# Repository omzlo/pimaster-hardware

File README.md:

# PiMaster HAT Hardware

This repository contains the design files and schematics of the Omzlo PiMaster HAT (Hardware Attached on Top).

See: http://omzlo.com/pimaster

This work is licensed under the [Creative Commons Attribution-ShareAlike 4.0 International Public License][1].

[1]: https://creativecommons.org/licenses/by-sa/4.0/

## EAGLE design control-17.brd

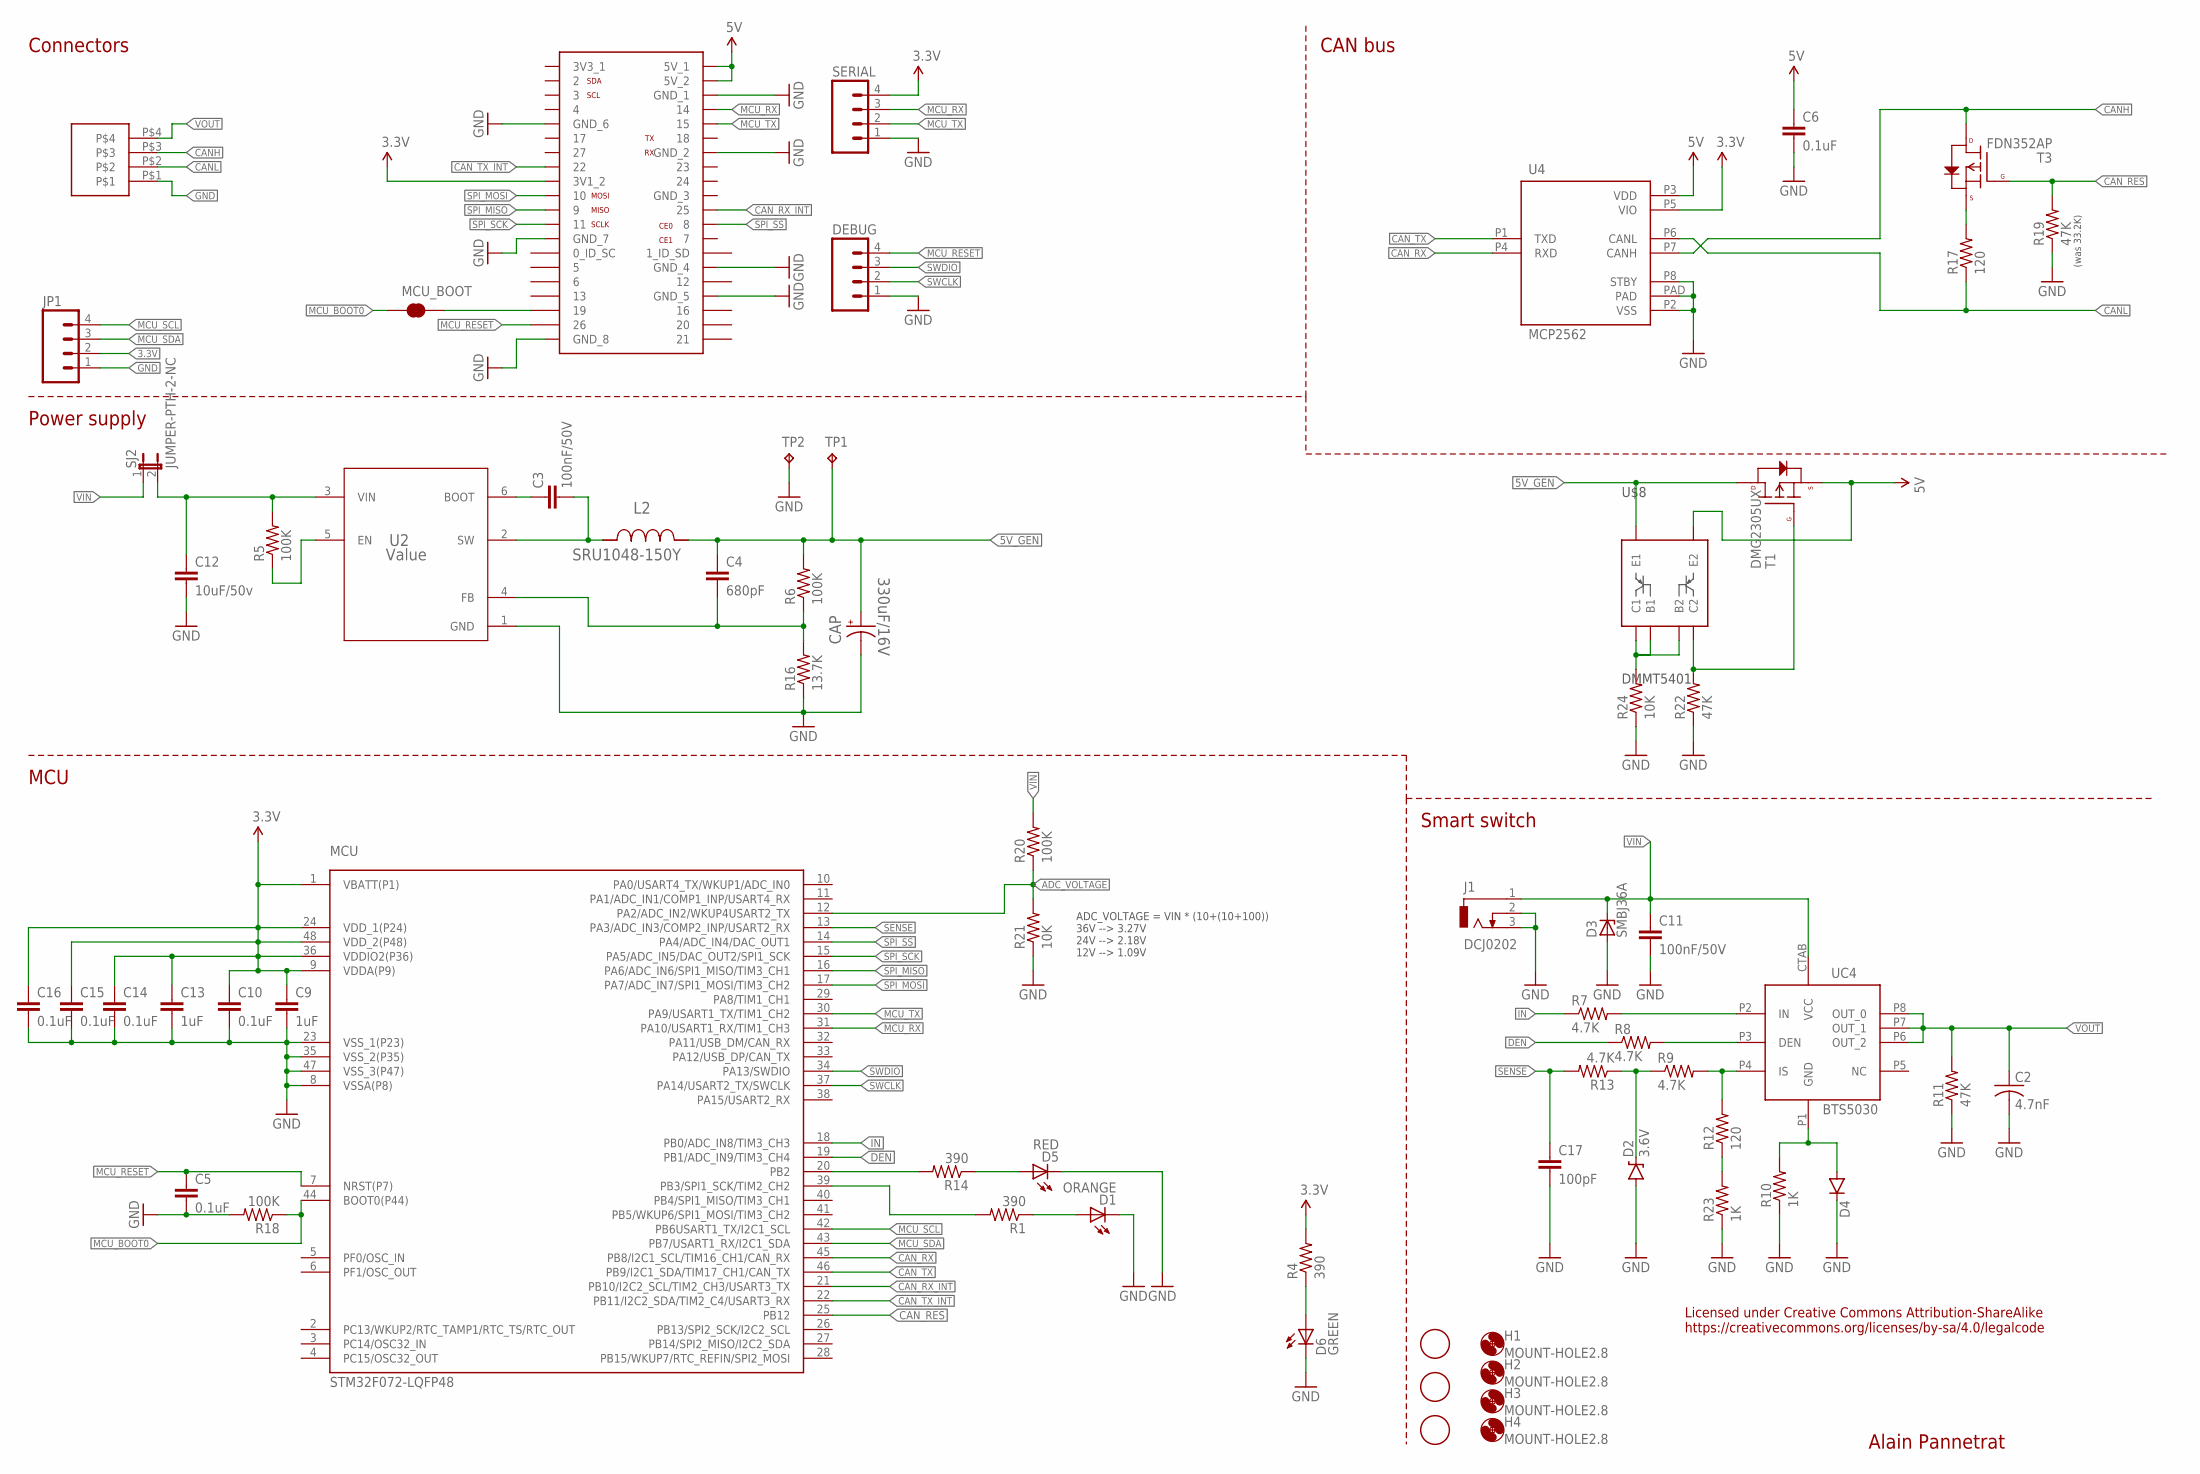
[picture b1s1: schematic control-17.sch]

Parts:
C2: 4.7nF; C0805
C3, C11: 100nF/50V; 0805
C4: 680pF; 0603-CAP
C5, C6, C10, C14, C15, C16: 0.1uF; 0603-CAP
C9, C13: 1uF; 0805
C12: 10uF/50v; 1206
C17: 100pF; 0805
CAP: 330uF/16V; PANASONIC_E
D1: ORANGE; CHIPLED_0805
D2: 3.6V; SOD-323
D3: SMBJ36A; SMB
D4: DIODESMA; SMA-DIODE
D5: RED; CHIPLED_0805
D6: GREEN; CHIPLED_0805
DEBUG: M04PTH; 1X04
H1, H2, H3, H4: MOUNT-HOLE2.8; 2,8
J1: DCJ0202
JP1: M04JST; 1X04-1.5MM_JST
L2: SRU1048-150Y; SRU1048
MCU: STM32F072-LQFP48; LQFP48
MCU_BOOT: JUMPER-PAD-2-NC_BY_TRACE; PAD-JUMPER-2-NC_BY_TRACE_YES_SILK
PI: RASPBERRY-PI-GPIO-SEPARATE; 2X20
R1, R4, R14: 390; R0603
R5, R6, R18, R20: 100K; R0603
R7, R8, R9, R13: 4.7K; R0805
R10, R23: 1K; R0805
R11, R19, R22: 47K; R0805
R12, R17: 120; R0805
R16: 13.7K; R0805
R21, R24: 10K; R0805
SERIAL: M04PTH; 1X04
SJ2: JUMPER-PTH-2-NC; PTH-JUMPER-NC_BOTTOM_NO_SILK
T1: DMG2305UX; SOT23-3
T3: FDN352AP; SOT23-3
TP1, TP2: TPPAD1-13; P1-13
U2: Value; DDC0006A_N
U4: MCP2562; DFN3X3
U$3: M04-PLUG-3.5
U$4, U$5, U$6: FIDUCIAL; FIDUCIAL_1MM
U$8: DMMT5401; SOT-23-6
UC4: BTS5030; PG-DSO-8-43

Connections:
3.3V: C9.1, C10.1, C13.1, C14.1, C15.1, C16.1, JP1.2, MCU.1 (VBATT(P1)), MCU.9 (VDDA(P9)), MCU.24 (VDD_1(P24)), MCU.36 (VDDIO2(P36)), MCU.48 (VDD_2(P48)), PI.17 (3V1_2), R4.2, SERIAL.4, U4.P5 (VIO)
3V3_1: PI.1 (3V3_1)
5V: C6.1, PI.2 (5V_1), PI.4 (5V_2), T1.2 (S), U4.P3 (VDD), U$8.5 (E2)
5V_GEN: C4.1, CAP.+, L2.2, R6.2, T1.3 (D), TP1.TP, U$8.6 (E1)
ADC_VOLTAGE: MCU.12 (PA2/ADC_IN2/WKUP4USART2_TX), R20.1, R21.2
CANH: T3.3 (D), U4.P7 (CANH), U$3.P$3
CANL: R17.1, U4.P6 (CANL), U$3.P$2
CAN_RES: MCU.25 (PB12), R19.2, T3.1 (G)
CAN_RX: MCU.45 (PB8/I2C1_SCL/TIM16_CH1/CAN_RX), U4.P4 (RXD)
CAN_RX_INT: MCU.21 (PB10/I2C2_SCL/TIM2_CH3/USART3_TX), PI.22 (25)
CAN_TX: MCU.46 (PB9/I2C1_SDA/TIM17_CH1/CAN_TX), U4.P1 (TXD)
CAN_TX_INT: MCU.22 (PB11/I2C2_SDA/TIM2_C4/USART3_RX), PI.15 (22)
DEN: MCU.19 (PB1/ADC_IN9/TIM3_CH4), R8.1
GND: C2.2, C5.2, C6.2, C9.2, C10.2, C11.2, C12.2, C13.2, C14.2, C15.2, C16.2, C17.2, CAP.-, D1.C, D2.A, D3.A, D4.C, D5.C, D6.C, DEBUG.1, J1.2, J1.3, JP1.1, MCU.8 (VSSA(P8)), MCU.23 (VSS_1(P23)), MCU.35 (VSS_2(P35)), MCU.47 (VSS_3(P47)), PI.6 (GND_1), PI.9 (GND_6), PI.14 (GND_2), PI.25 (GND_7), PI.30 (GND_4), PI.34 (GND_5), PI.39 (GND_8), R10.1, R11.1, R16.1, R18.2, R19.1, R21.1, R22.1, R23.1, R24.1, SERIAL.1, TP2.TP, U2.1 (GND), U4.P2 (VSS), U4.P8 (STBY), U4.PAD, U$3.P$1
IN: MCU.18 (PB0/ADC_IN8/TIM3_CH3), R7.1
MCU_BOOT0: MCU.44 (BOOT0(P44)), MCU_BOOT.1, R18.1
MCU_RESET: C5.1, DEBUG.4, MCU.7 (NRST(P7)), PI.37 (26)
MCU_RX: MCU.31 (PA10/USART1_RX/TIM1_CH3), PI.8 (14), SERIAL.3
MCU_SCL: JP1.4, MCU.42 (PB6USART1_TX/I2C1_SCL)
MCU_SDA: JP1.3, MCU.43 (PB7/USART1_RX/I2C1_SDA)
MCU_TX: MCU.30 (PA9/USART1_TX/TIM1_CH2), PI.10 (15), SERIAL.2
unnamed: D2.C, R9.1, R13.1
unnamed: D1.A, R1.1
unnamed: R7.2, UC4.P2 (IN)
unnamed: MCU_BOOT.2, PI.35 (19)
unnamed: R5.1, U2.5 (EN)
unnamed: C12.1, R5.2, SJ2.2, U2.3 (VIN)
unnamed: C4.2, R6.1, R16.2, U2.4 (FB)
unnamed: R12.1, R23.2
unnamed: R8.2, UC4.P3 (DEN)
unnamed: MCU.20 (PB2), R14.2
unnamed: R17.2, T3.2 (S)
unnamed: R9.2, R12.2, UC4.P4 (IS)
unnamed: D4.A, R10.2, UC4.P1 (GND)
unnamed: MCU.39 (PB3/SPI1_SCK/TIM2_CH2), R1.2
unnamed: C3.2, L2.1, U2.2 (SW)
unnamed: D5.A, R14.1
unnamed: C3.1, U2.6 (BOOT)
unnamed: D6.A, R4.1
unnamed: R24.2, U$8.1 (C1), U$8.2 (B1), U$8.3 (B2)
unnamed: R22.2, T1.1 (G), U$8.4 (C2)
SENSE: C17.1, MCU.13 (PA3/ADC_IN3/COMP2_INP/USART2_RX), R13.2
SPI_MISO: MCU.16 (PA6/ADC_IN6/SPI1_MISO/TIM3_CH1), PI.21 (9)
SPI_MOSI: MCU.17 (PA7/ADC_IN7/SPI1_MOSI/TIM3_CH2), PI.19 (10)
SPI_SCK: MCU.15 (PA5/ADC_IN5/DAC_OUT2/SPI1_SCK), PI.23 (11)
SPI_SS: MCU.14 (PA4/ADC_IN4/DAC_OUT1), PI.24 (8)
SWCLK: DEBUG.2, MCU.37 (PA14/USART2_TX/SWCLK)
SWDIO: DEBUG.3, MCU.34 (PA13/SWDIO)
VIN: C11.1, D3.C, J1.1, R20.2, SJ2.1, UC4.CTAB (VCC)
VOUT: C2.1, R11.2, U$3.P$4, UC4.P6 (OUT_2), UC4.P7 (OUT_1), UC4.P8 (OUT_0)

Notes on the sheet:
Alain Pannetrat
ADC_VOLTAGE = VIN * (10+(10+100)) 36V --> 3.27V 24V --> 2.18V 12V --> 1.09V
(was 33.2K)
Power supply
MCU
Smart switch
CAN bus
Connectors
Licensed under Creative Commons Attribution-ShareAlike https://creativecommons.org/licenses/by-sa/4.0/legalcode

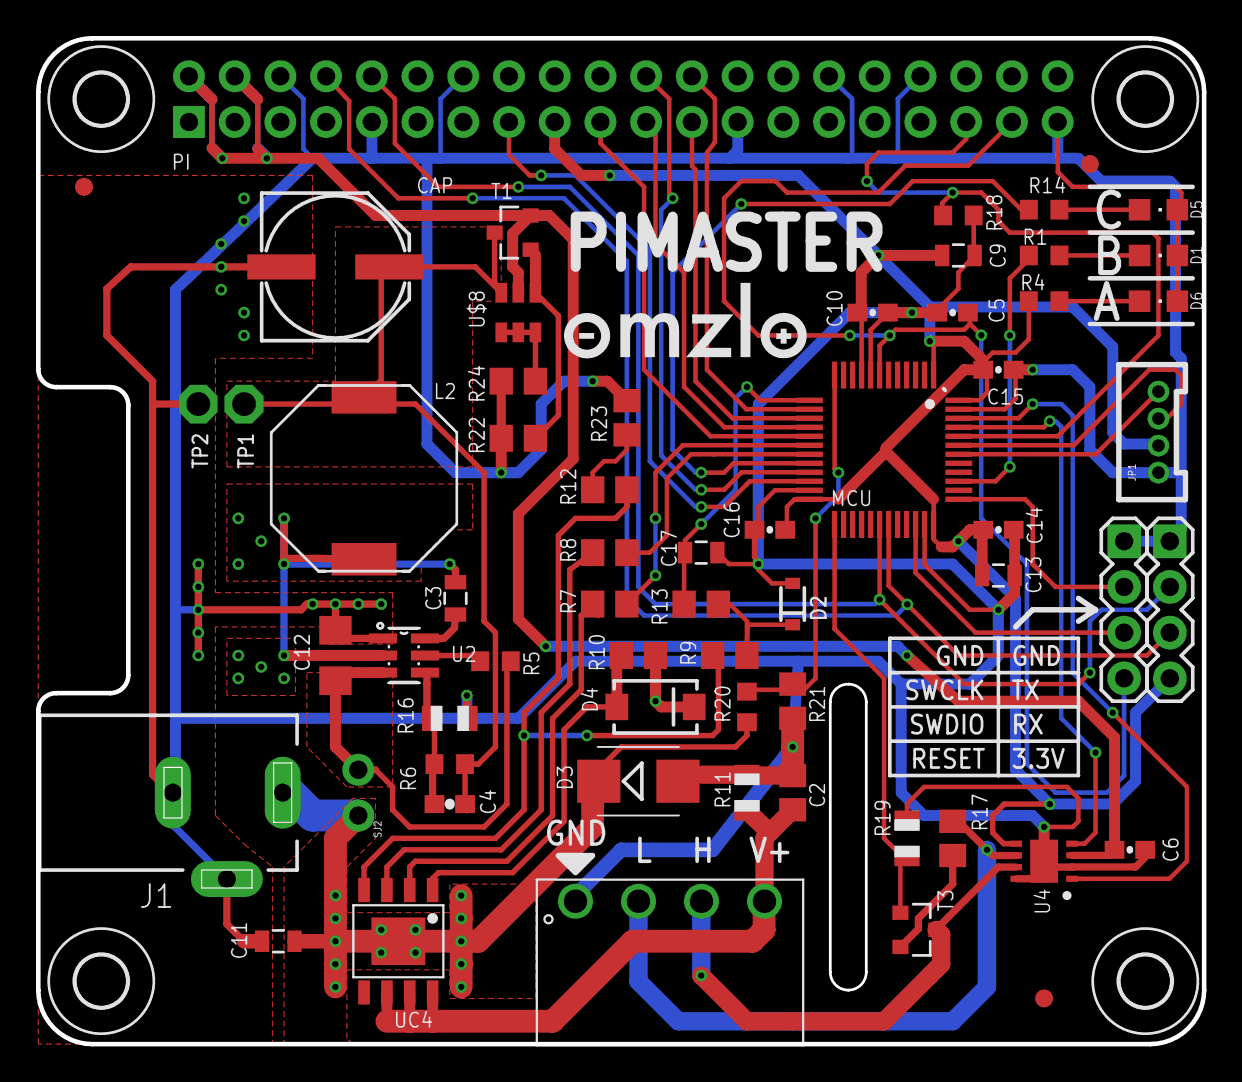
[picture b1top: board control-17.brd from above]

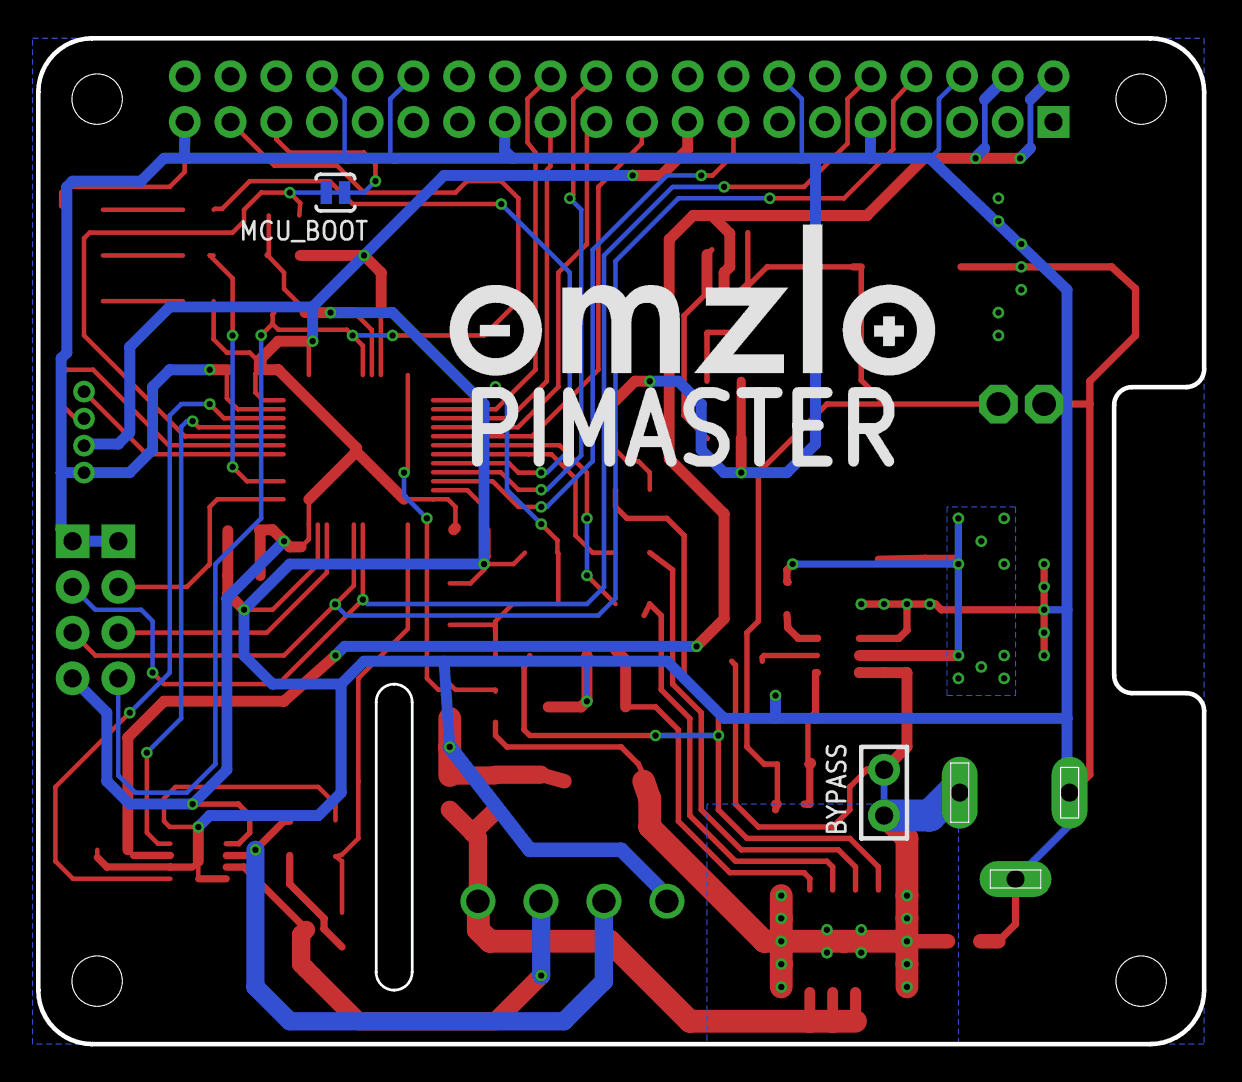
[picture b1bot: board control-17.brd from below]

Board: 2 copper layers, 64.8 x 55.9 mm, 69 parts (2 on the bottom side), 49 nets.

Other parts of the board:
U$1: OMZLO-0.5
U$2: OMZLO

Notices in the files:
parts and their libraries:
SparkFun-DiscreteSemi: Licensing: Creative Commons ShareAlike 4.0 International - https://creativecommons.org/licenses/by-sa/4.0
